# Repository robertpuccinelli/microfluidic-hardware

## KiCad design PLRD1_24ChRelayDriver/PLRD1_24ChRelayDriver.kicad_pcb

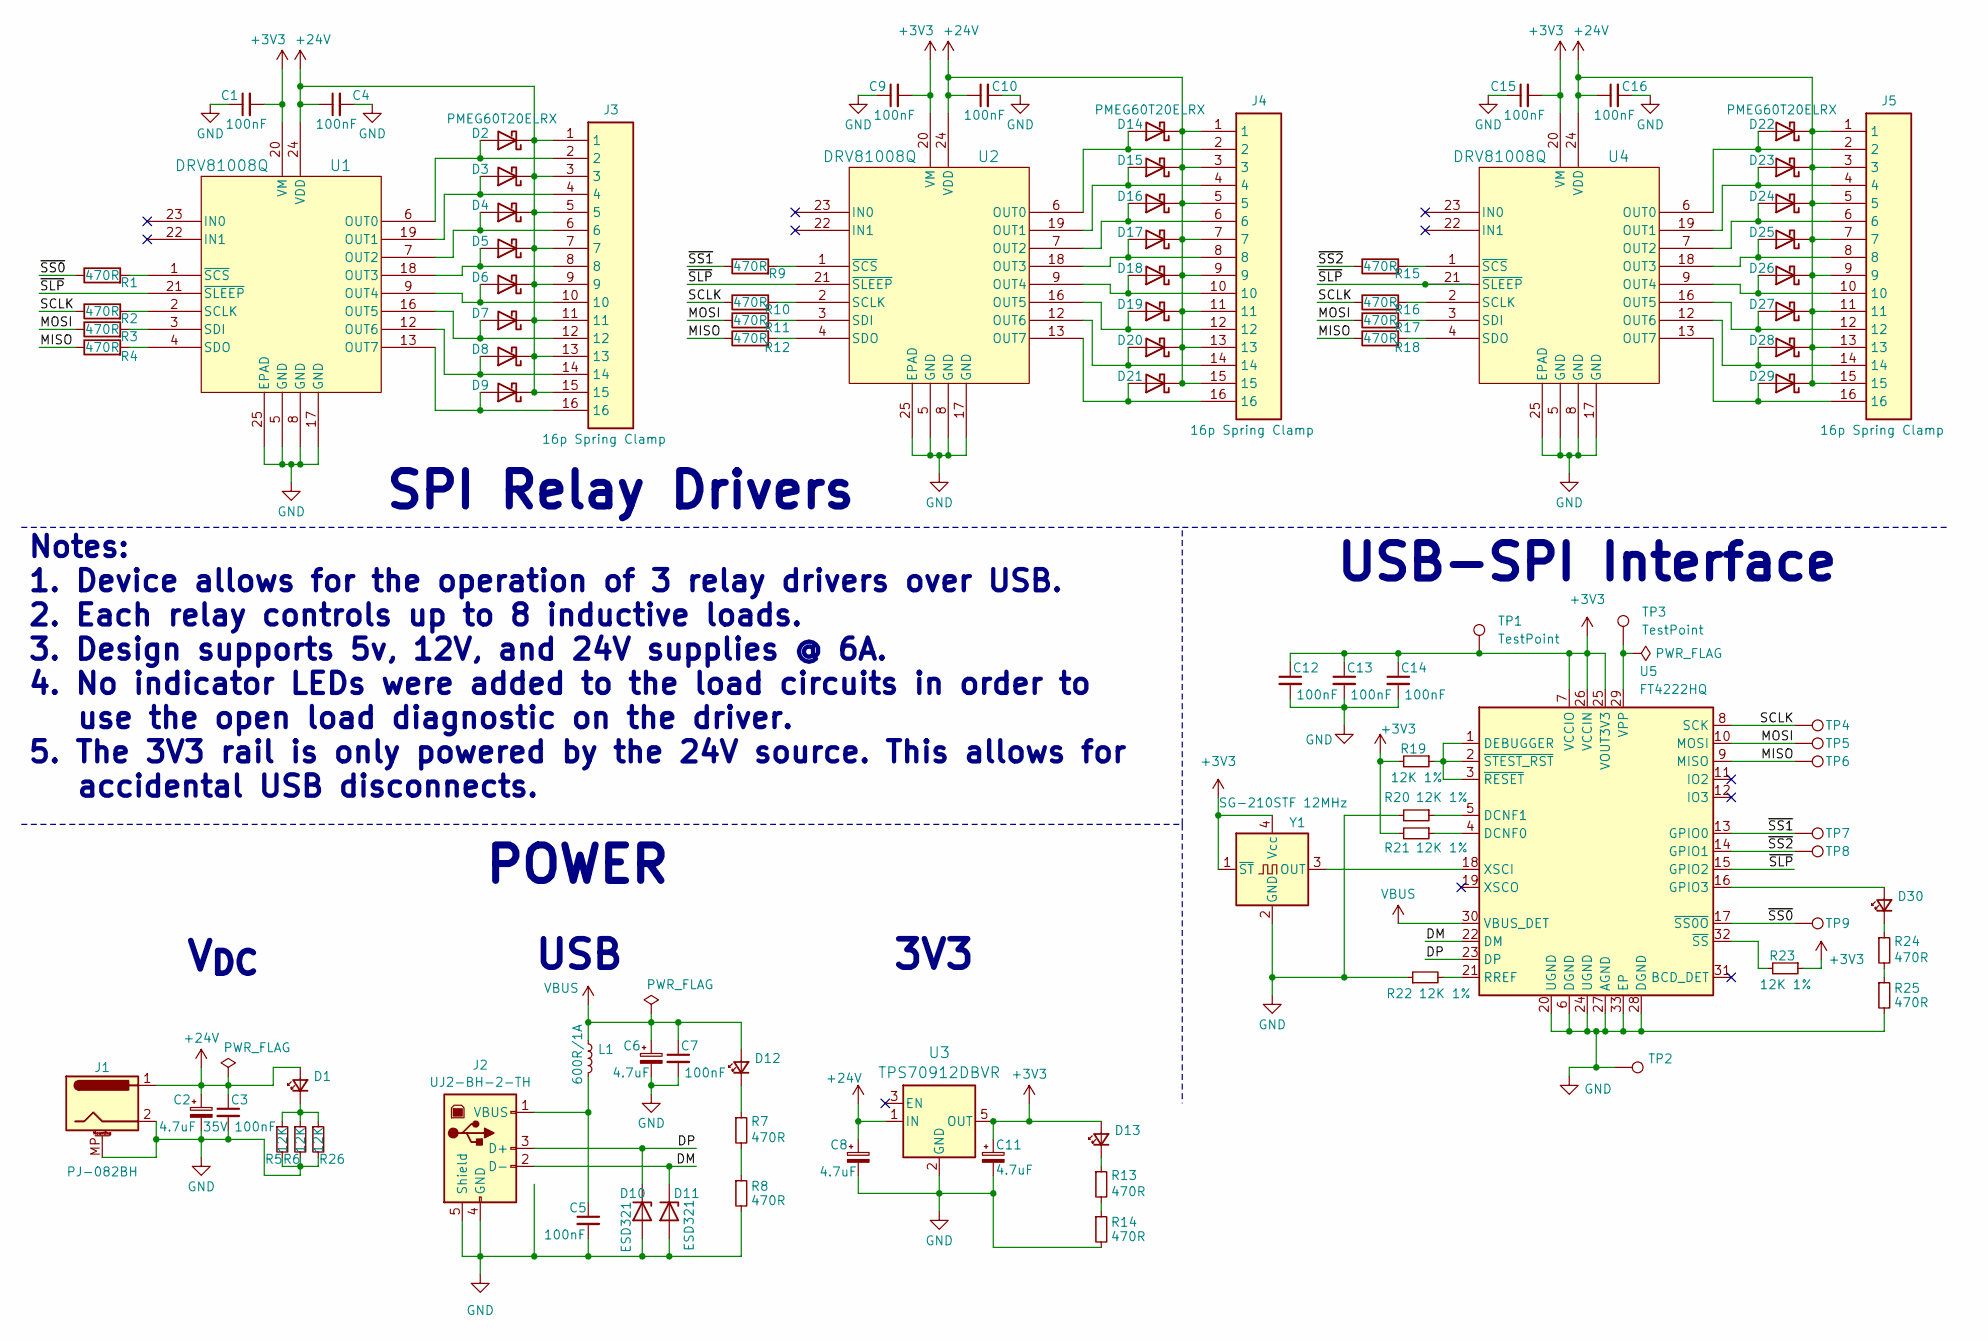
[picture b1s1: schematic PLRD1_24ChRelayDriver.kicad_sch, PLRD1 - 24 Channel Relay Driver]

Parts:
C1, C3, C4, C5, C7, C9, C10, C12, C13, C14, C15, C16: 100nF; C_0402_1005Metric
C2: 4.7uF 35V; CP_EIA-3528-21_Kemet-B
C6, C8, C11: 4.7uF; CP_EIA-3528-21_Kemet-B
D1, D12, D13, D30: SML-P11UTT86R; LED_0402_1005Metric
D2, D3, D4, D5, D6, D7, D8, D14, D15, D16, D17, D18, D19, D20, D22, D23, D24, D25, D26, D27, D28: MBR0580; D_SOD-123
D9, D21, D29: PMEG60T20ELRX; D_SOD-123
D10, D11: ESD321; D_SOD-523
J1: PJ-082BH; CUI_PJ-082BH
J2: UJ2-BH-2-TH; CUI_UJ2-BH-2-TH
J3, J4, J5: 16p Spring Clamp; 1989887; Manufacturer_Part_Number 1989887; Mouser Part Number 651-1989887
L1: 600R/1A; L_0402_1005Metric
R1, R2, R3, R4, R7, R8, R9, R10, R11, R12, R13, R14, R15, R16, R17, R18, R24, R25: 470R; R_0402_1005Metric
R5, R6, R26: 12K; R_0402_1005Metric
R19, R20, R21, R22, R23: 12K 1%; R_0402_1005Metric
TP1, TP2, TP3, TP4, TP5, TP6, TP7, TP8, TP9: TestPoint; TestPoint_THTPad_1.0x1.0mm_Drill0.5mm
U1, U2, U4: DRV81008Q; HTSSOP24_PWP-T_TEX
U3: TPS70912DBVR; DBV5_TEX
U5: FT4222HQ; VQFN-32-1EP_5x5mm_P0.5mm_EP3.1x3.1mm
Y1: SG-210STF 12MHz; Oscillator_SMD_SeikoEpson_SG210-4Pin_2.5x2.0mm

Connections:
+3V3: C1.2, C9.2, C11.1, C12.1, C13.1, C14.1, C15.2, D13.2 (A), R19.2, R21.2, R23.1, TP1.1, U1.20 (VM), U2.20 (VM), U3.5 (OUT), U4.20 (VM), U5.7 (VCCIO), U5.25 (VOUT3V3), U5.26 (VCCIN), Y1.1 (~ST), Y1.4 (Vcc)
+24V: C2.1, C3.1, C4.1, C8.1, C10.1, C16.1, D1.2 (A), D2.1 (K), D3.1 (K), D4.1 (K), D5.1 (K), D6.1 (K), D7.1 (K), D8.1 (K), D9.1 (K), D14.1 (K), D15.1 (K), D16.1 (K), D17.1 (K), D18.1 (K), D19.1 (K), D20.1 (K), D21.1 (K), D22.1 (K), D23.1 (K), D24.1 (K), D25.1 (K), D26.1 (K), D27.1 (K), D28.1 (K), D29.1 (K), J1.1, J3.1, J3.3, J3.5, J3.7, J3.9, J3.11, J3.13, J3.15, J4.1, J4.3, J4.5, J4.7, J4.9, J4.11, J4.13, J4.15, J5.1, J5.3, J5.5, J5.7, J5.9, J5.11, J5.13, J5.15, U1.24 (VDD), U2.24 (VDD), U3.1 (IN), U4.24 (VDD)
/DM: D11.1 (K), J2.2 (D-), U5.22 (DM)
/DP: D10.1 (K), J2.3 (D+), U5.23 (DP)
/MISO: R4.1, R12.1, R18.1, TP6.1, U5.9 (MISO)
/MOSI: R3.1, R11.1, R17.1, TP5.1, U5.10 (MOSI)
/SCLK: R2.1, R10.1, R16.1, TP4.1, U5.8 (SCK)
/~SLP: U1.21 (~SLEEP), U2.21 (~SLEEP), U4.21 (~SLEEP), U5.15 (GPIO2)
/~SS0: R1.1, TP9.1, U5.17 (~SS0O)
/~SS1: R9.1, TP7.1, U5.13 (GPIO0)
/~SS2: R15.1, TP8.1, U5.14 (GPIO1)
GND: C1.1, C2.2, C3.2, C4.2, C5.2, C6.2, C7.2, C8.2, C9.1, C10.2, C11.2, C12.2, C13.2, C14.2, C15.1, C16.2, D10.2 (A), D11.2 (A), J1.2, J1.MP (MountPin), J2.4 (GND), J2.5 (Shield), R5.2, R6.2, R8.2, R14.2, R20.2, R22.1, R25.2, R26.2, TP2.1, U1.5 (GND), U1.8 (GND), U1.17 (GND), U1.25 (EPAD), U2.5 (GND), U2.8 (GND), U2.17 (GND), U2.25 (EPAD), U3.2 (GND), U4.5 (GND), U4.8 (GND), U4.17 (GND), U4.25 (EPAD), U5.6 (DGND), U5.20 (UGND), U5.24 (UGND), U5.27 (AGND), U5.28 (DGND), U5.33 (EP), Y1.2 (GND)
unnamed: D1.1 (K), R5.1, R6.1, R26.1
unnamed: D2.2 (A), J3.2, U1.6 (OUT0)
unnamed: D3.2 (A), J3.4, U1.19 (OUT1)
unnamed: D4.2 (A), J3.6, U1.7 (OUT2)
unnamed: D5.2 (A), J3.8, U1.18 (OUT3)
unnamed: D6.2 (A), J3.10, U1.9 (OUT4)
unnamed: D7.2 (A), J3.12, U1.16 (OUT5)
unnamed: D8.2 (A), J3.14, U1.12 (OUT6)
unnamed: D9.2 (A), J3.16, U1.13 (OUT7)
unnamed: D12.1 (K), R7.1
unnamed: D13.1 (K), R13.1
unnamed: D14.2 (A), J4.2, U2.6 (OUT0)
unnamed: D15.2 (A), J4.4, U2.19 (OUT1)
unnamed: D16.2 (A), J4.6, U2.7 (OUT2)
unnamed: D17.2 (A), J4.8, U2.18 (OUT3)
unnamed: D18.2 (A), J4.10, U2.9 (OUT4)
unnamed: D19.2 (A), J4.12, U2.16 (OUT5)
unnamed: D20.2 (A), J4.14, U2.12 (OUT6)
unnamed: D21.2 (A), J4.16, U2.13 (OUT7)
unnamed: D22.2 (A), J5.2, U4.6 (OUT0)
unnamed: D23.2 (A), J5.4, U4.19 (OUT1)
unnamed: D24.2 (A), J5.6, U4.7 (OUT2)
unnamed: D25.2 (A), J5.8, U4.18 (OUT3)
unnamed: D26.2 (A), J5.10, U4.9 (OUT4)
unnamed: D27.2 (A), J5.12, U4.16 (OUT5)
unnamed: D28.2 (A), J5.14, U4.12 (OUT6)
unnamed: D29.2 (A), J5.16, U4.13 (OUT7)
unnamed: D30.2 (A), U5.16 (GPIO3)
unnamed: D30.1 (K), R24.1
unnamed: C5.1, J2.1 (VBUS), L1.2
unnamed: R7.2, R8.1
unnamed: R13.2, R14.1
unnamed: R24.2, R25.1
unnamed: R2.2, U1.2 (SCLK)
unnamed: R3.2, U1.3 (SDI)
unnamed: R4.2, U1.4 (SDO)
unnamed: R1.2, U1.1 (~SCS)
unnamed: R10.2, U2.2 (SCLK)
unnamed: R11.2, U2.3 (SDI)
unnamed: R12.2, U2.4 (SDO)
unnamed: R9.2, U2.1 (~SCS)
unnamed: R16.2, U4.2 (SCLK)
unnamed: R17.2, U4.3 (SDI)
unnamed: R18.2, U4.4 (SDO)
unnamed: R15.2, U4.1 (~SCS)
unnamed: R21.1, U5.4 (DCNF0)
unnamed: R20.1, U5.5 (DCNF1)
unnamed: R19.1, U5.1 (DEBUGGER), U5.2 (~STEST_RST), U5.3 (~RESET)
unnamed: R22.2, U5.21 (RREF)
unnamed: TP3.1, U5.29 (VPP)
unnamed: U5.18 (XSCI), Y1.3 (OUT)
unnamed: R23.2, U5.32 (~SS)
VBUS: C6.1, C7.1, D12.2 (A), L1.1, U5.30 (VBUS_DET)

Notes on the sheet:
3V3
V_{DC}
SPI Relay Drivers
USB-SPI Interface
USB
Notes: 1. Device allows for the operation of 3 relay drivers over USB. 2. Each relay controls up to 8 inductive loads. 3. Design supports 5v, 12V, and 24V supplies @ 6A. 4. No indicator LEDs were added to the load circuits in order to use the open load diagnostic on the driver. 5. The 3V3 rail is o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
POWER

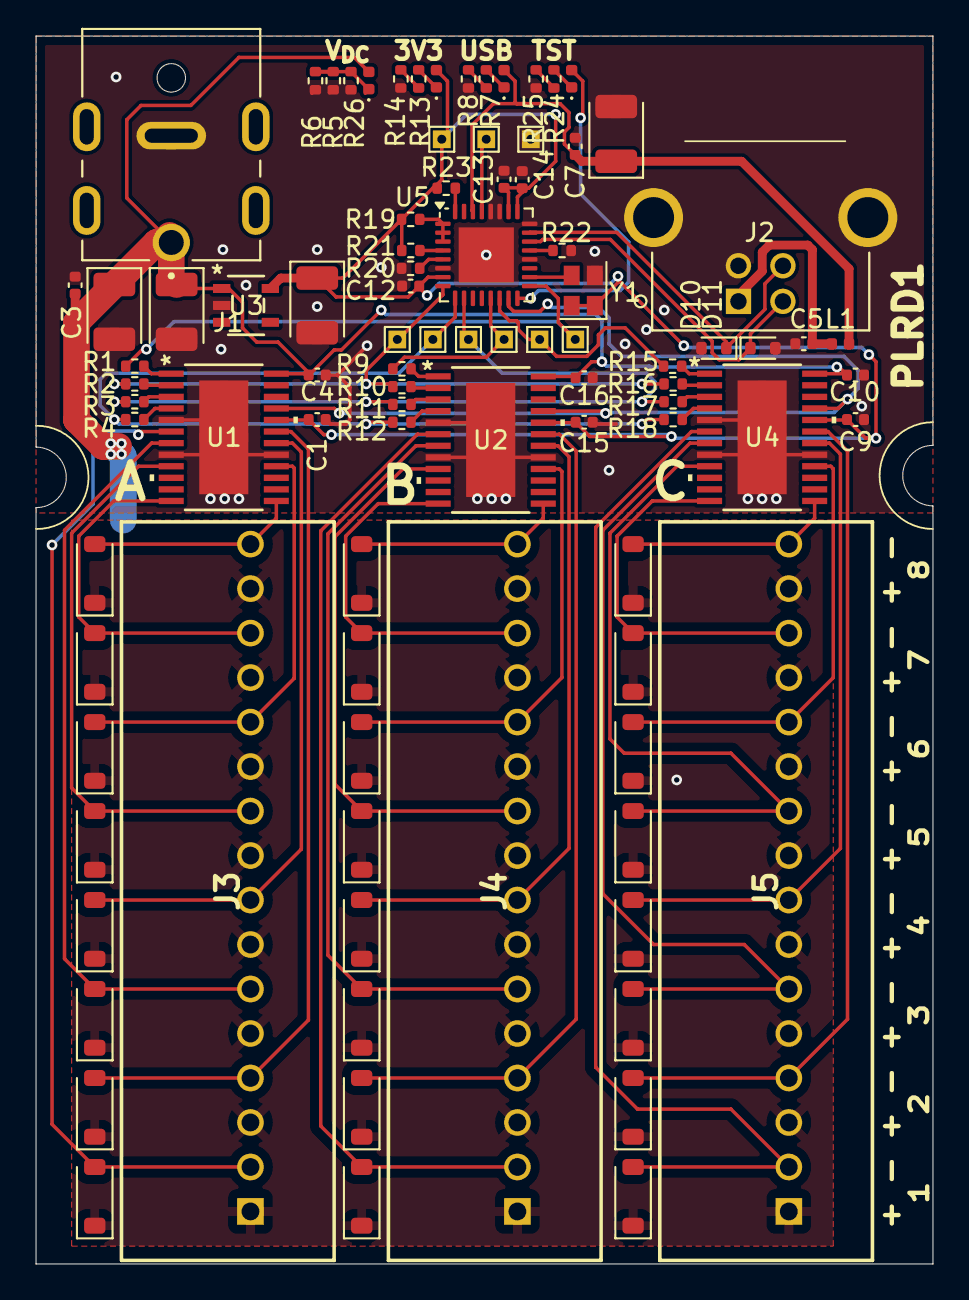
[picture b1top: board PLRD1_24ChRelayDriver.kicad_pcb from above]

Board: 2 copper layers, 50.4 x 69.0 mm, 93 parts (0 on the bottom side), 65 nets.

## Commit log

2025-02-05 Init repo, start design of relay driver board
2025-02-06 Continue editing Rev A
2025-02-06 Rev A intermediate
2025-02-14 PLRD1 Relay Driver Rev A
